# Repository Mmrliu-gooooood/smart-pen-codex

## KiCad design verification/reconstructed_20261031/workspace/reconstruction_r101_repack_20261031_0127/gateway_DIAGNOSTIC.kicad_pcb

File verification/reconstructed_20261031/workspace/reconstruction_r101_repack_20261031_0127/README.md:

# NEW R101/PICKUP + R503 bounded repack proposal
From actual recovered4d7d CAD contexts and local gateway diagnostic snapshot (exact hash in paths_results). No missing late artifacts claimed. No source/frozen edits, NOFAB / NO POWER.

Simultaneous full R101 F(2.1,20)0°, unchanged10k 1%,2.45×.95×1.45; R503 B(8,16.5)0°,2.45×.95×1.45. All four restored corrected-support CAD contexts retain104 envelopes; zero new collisions. Minimum .5130156335 mm R101 to ACCESS19 upper cover; opposite R503/C104 .93 mm budget separation. Wrong-face negative control detects overlap. In-memory only, not saved final-pose CAD/STEP.

Prospective PICKUP path has finite .240 mm gap to full R101. Newly occupied .4×.95 R101 strip has no undeleted same-face track/via. New CHIP_EN lead only shifted pad1, AON .3 F lead to Ø.6/.3 via(3.1,21); D0 outlet Ø.45/.2 at(2.4,21) also screened. Ordinary courtyard projections kept separate.

PICKUP subset(2.675,23.3)→(2.675,24.375) remains beneath R213. It is NOT a zero-body-overlap claim: exact native oldsame-net track UUID7da52644-9f2c-5d36-ab82-77ad53a112d5 contains entire finite new subset, added area0. Shifted subset+.15X negative yields positive added area. This inheritance is not manufacturing/solder qualification or a new underbody waiver. All other nonterminal fullbody/Fab intrusion absent.

Run placement.py and paths.py with /usr/bin/python3. Normal/-O JSON byte-identical. Whole electrical/source/copper/reference/final native gates remain outside this proposal; actual combined native separately screened in0128.

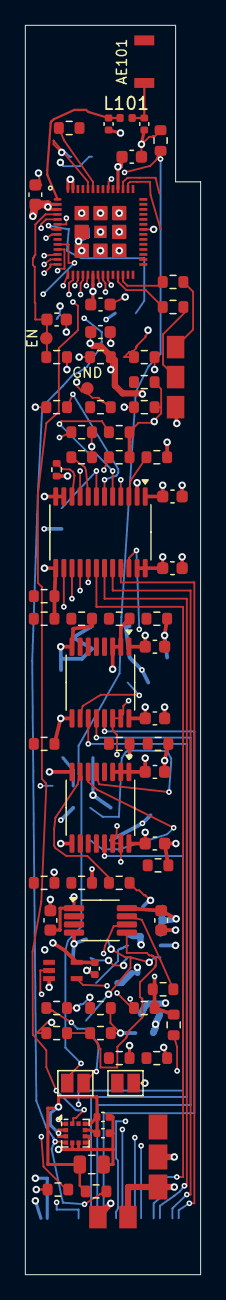
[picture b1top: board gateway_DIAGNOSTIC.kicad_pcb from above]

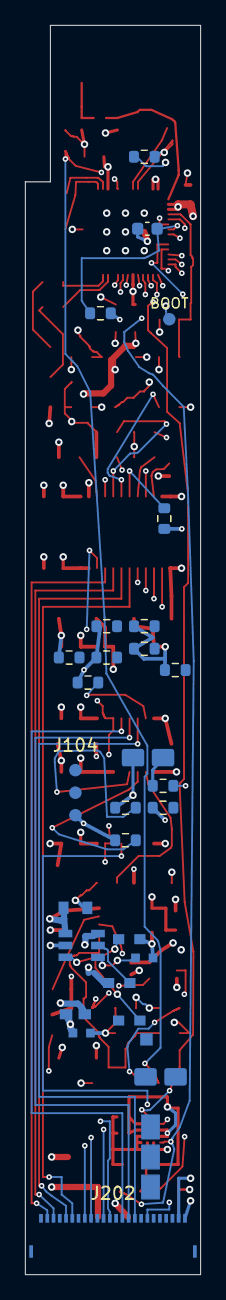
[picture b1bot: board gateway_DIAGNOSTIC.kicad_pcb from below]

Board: 6 copper layers, 14.0 x 99.8 mm, 103 parts (29 on the bottom side), 70 nets.

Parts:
AE101: 2450AT18A0100001E_STUDY_NOFAB; Johanson_2450AT18A0100001E_Rev4_Study_NOFAB
C101: 1u; C_0603_1608Metric
C102: 22u; C_0603_1608Metric
C103, C104, C105: 100n; C_0603_1608Metric
C106, C107: DNP RF_TUNE; C_0402_1005Metric
C201, C202, C203, C204, C205, C206, C207, C208: 100n X7R; C_0603_1608Metric
C209, C501, C502: 100nF 16V X7R +/-10%; C_0402_1005Metric
C301: 10uF 10V X7R; C1_TDK_0805_X7R_STANDARD
C302: 1uF 10V X7R; C2_TDK_0603_STUDY
C303: 1nF 25V C0G; C3_TDK_0603_STUDY
C503: 10uF 10V X7R +/-10%; C_0805_2012Metric
C504: 1n C0G; C_0603_1608Metric
J103: DRY CONTACT PADS; WireLands2_P2.4
J104: UART_SERVICE_CAMERA_OFF_ONLY; Probe3_P1.8_NoPaste
J105: ADC_SAFE_FRONTEND_LINK_NOT_RAW_BATTERY; WireLands2_P2.4
J106: POWER_CORE; J106_Wirebank_PRELAYOUT
J107: CHARGER_MODE; J107_Wirebank_PRELAYOUT
J108: SERVICE_EN_BOOT_GND; ServiceProbe3_NOFAB
J109: USB_TAIL_LINK; USBWireLands3_14mm_PRELAYOUT
J202: 5034802400_NEW_24PIN_SENSOR_HANDOFF; Molex_5034802400_24P_P0.5_CANDIDATE
J301: APPROVED LOAD / TBD; J301_Wirebank_PRELAYOUT
JP201: DNP_IO_COMMISSION; SolderJumper-2_P1.3mm_Open_Pad1.0x1.5mm
JP202: DNP_SCCB_COMMISSION; SolderJumper-2_P1.3mm_Open_Pad1.0x1.5mm
JP301: OPEN / DO NOT BRIDGE; Commission_OPEN_NO_PASTE
L101: RF_MATCH_TBD; L_0402_1005Metric
R101, R102, R103, R104, R105, R202, R203, R206, R207, R501, R502: 10k 1%; R_0603_1608Metric
R106, R107, R108, R109, R210, R211, R212, R213, R214, R215, R216, R218, R219, R220, R221, R222, R223, R224, R225, R226, R227, R228, R229, R230, R231, R232, R233, R234, R235, R237: 100k 1%; R_0603_1608Metric
R112, R113: 22R SI_TBD; R_0603_1608Metric
R201, R504: 1k 1%; R_0603_1608Metric
R204: 100R 1%; R_0603_1608Metric
R205: 4.7k 1%; R_0603_1608Metric
R217: 100k 1%; R_0402_1005Metric
R236: 4.7k 1% RESET_CANDIDATE; R_0603_1608Metric
R240, R241, R242, R243: 10k 1% INITIAL_100kHz; R_0603_1608Metric
R301: 100k 1%; R1_YAGEO_0603_STUDY
R302: 1k 1%; R2_YAGEO_0603_STUDY
R303: 100R 1%; R3_YAGEO_0603_STUDY
R503: 47k 1%; R_0603_1608Metric
TP301: ENABLE MEASURE; Enable_measure_land
U101: ESP32-S3-PICO-1-N8R8; ESP32-S3-PICO-1_LGA57_7x7_P0.4_OfficialDerived_NOFAB
U201: SN74AXC8T245PWR; TSSOP-24_4.4x7.8mm_P0.65mm
U202, U203: SN74AXC4T245PWR; TSSOP-16_4.4x5mm_P0.65mm
U204: TCA9517DGKR; VSSOP-8_3x3mm_P0.65mm
U205: SN74LVC1G14DCKR; TI_DCK0005A_Schmitt_OfficialLand
U301: TPS22918DBVR; TPS22918_DBV_TI_1p1x0p6
U501: LIS2DW12TR; LGA-12_2x2mm_P0.5mm

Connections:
3V3_AON: C102.1, C103.1, C104.1, C105.1, C201.1, C203.1, C205.1, C207.1, C209.1, C301.1, C501.1, C502.1, C503.1, J106.2, R101.2, R102.2, R103.2, R203.2, R240.2, R241.2, R501.1, R502.1, R503.1, U101.2, U101.3, U101.20, U101.46, U101.55, U101.56, U201.1, U202.1, U203.1, U203.2, U203.3, U204.8, U205.5 (VCC), U301.1, U501.2, U501.3, U501.9, U501.10
AON_I2C_SCL: R501.2, U101.10, U501.1
AON_I2C_SDA: R502.2, U101.11, U501.4
BATTERY_ADC: J105.1, U101.9
BOOT_N: J108.2, R102.1, U101.5
CAM_3V3_PRELINK: C302.1, JP301.1, R303.1, U301.6
CAM_3V3_SW: J301.1, JP301.2
CAM_BUS_EN: JP202.1, R108.1, U101.37
CAM_CT: C303.1, U301.4
CAM_D0: R210.1, U101.12, U201.3
CAM_D1: R211.1, U101.13, U201.4
CAM_D2: R212.1, U101.14, U201.5
CAM_D3: R213.1, U101.15, U201.6
CAM_D4: R214.1, U101.16, U201.7
CAM_D5: R215.1, U101.17, U201.8
CAM_D6: R216.1, U101.18, U201.9
CAM_D7: R217.1, U101.19, U201.10
CAM_HREF: R220.1, U101.23, U202.6
CAM_IO_EN: JP201.1, R107.1, U101.48
CAM_ISO_OE_N: R203.1, U201.22, U202.14, U202.15, U203.14, U203.15, U205.4 (Y)
CAM_ON: R301.1, R302.2, U301.3
CAM_PCLK: R218.1, U101.21, U202.4
CAM_PWDN_UART_RX: J104.2, R223.1, U101.50, U203.6
CAM_PWR_EN: R106.1, R302.1, TP301.1, U101.47
CAM_QOD: R303.2, U301.5
CAM_RESET_UART_TX: J104.1, R222.1, U101.49, U203.5
CAM_SCL: R240.1, U101.44, U204.7
CAM_SDA: R241.1, U101.45, U204.6
CAM_VSYNC: R219.1, U101.22, U202.5
CAM_XCLK: R221.1, U101.43, U203.4
CHIP_EN: C101.1, J108.1, R101.1, U101.4
CONTACT: J103.1, R504.2
GND: C101.2, C102.2, C103.2, C104.2, C105.2, C106.2, C107.2, C201.2, C202.2, C203.2, C204.2, C205.2, C206.2, C207.2, C208.2, C209.2, C301.2, C302.2, C303.2, C501.2, C502.2, C503.2, C504.2, J103.2, J104.3, J105.2, J106.3, J107.3, J108.3, J109.3, J202.1, J202.4, J202.7, J202.10, J202.13, J202.17, J202.24, J301.2, R104.2, R105.2, R106.2, R107.2, R108.2, R109.2, R202.2, R205.2, R206.2, R207.2, R210.2, R211.2, R212.2, R213.2, R214.2, R215.2, R216.2, R217.2, R218.2, R219.2, R220.2, R221.2, R222.2, R223.2, R224.2, R225.2, R226.2, R227.2, R228.2, R229.2, R230.2, R231.2, R232.2, R233.2, R234.2, R235.2, R236.2, R237.2, R301.2, U101.57, U201.2, U201.11, U201.12, U201.13, U202.2, U202.3, U202.8, U202.9, U203.8, U203.9, U204.4, U205.3 (GND), U301.2, U501.5, U501.6, U501.7, U501.8
ILLUM_STROBE: R109.1, U101.36
IO_ENABLE_LINK: JP201.2, R201.1
ISO_GATE: R201.2, R202.1, U205.2 (A)
NIB_CONTACT_N: C504.1, R503.2, R504.1, U101.7
PICKUP_INT_N: U101.6, U501.12
RF_ANT: AE101.1, C107.1, L101.2
RF_SIP: C106.1, L101.1, U101.1
SCCB_ENABLE_LINK: JP202.2, R204.1
SCCB_EN_SAFE: R204.2, R205.1, U204.5
SENS_D0: J202.2, R224.1, U201.21
SENS_D1: J202.3, R225.1, U201.20
SENS_D2: J202.5, R226.1, U201.19
SENS_D3: J202.6, R227.1, U201.18
SENS_D4: J202.8, R228.1, U201.17
SENS_D5: J202.9, R229.1, U201.16
SENS_D6: J202.11, R230.1, U201.15
SENS_D7: J202.12, R231.1, U201.14
SENS_EXTCLK: J202.18, R235.1, U203.13
SENS_HREF: J202.16, R234.1, U202.11
SENS_PCLK: J202.14, R232.1, U202.13
SENS_SCL: J202.21, R242.1, U204.2
SENS_SDA: J202.22, R243.1, U204.3
SENS_TRIG_IN: J202.20, R237.1, U203.11
SENS_VIO_1V8: C202.1, C204.1, C206.1, C208.1, J202.23, R242.2, R243.2, U201.23, U201.24, U202.16, U203.16, U204.1
SENS_VSYNC: J202.15, R233.1, U202.12
SENS_XSHUTDN_N: J202.19, R236.1, U203.12
STRAP_GPIO3: R103.1, U101.8
STRAP_GPIO45: R104.1, U101.51
STRAP_GPIO46: R105.1, U101.52
UNUSED_A_INPUT: R207.1, U203.7
UNUSED_B_INPUT: R206.1, U202.10
USB_DM: J109.2, R113.1
USB_DM_MCU: R113.2, U101.25
USB_DP: J109.1, R112.1
USB_DP_MCU: R112.2, U101.26
USB_EN1: J107.1, U101.24
USB_EN2: J107.2, U101.27
